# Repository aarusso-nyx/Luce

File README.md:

# Luce Firmware

ESP32 firmware project built with PlatformIO + ESP-IDF.

> `scripts/luce.sh` refreshes PlatformIO discovery, including sourcing your `~/.zshrc` environment when required.

## Build/Flash/Monitor

Use the repository scripts for deterministic local workflows:

```bash
source ~/.zshrc
./scripts/luce.sh build                    # build all environments
./scripts/luce.sh upload --env default      # flash a specific environment
./scripts/luce.sh monitor --env default     # serial monitor with timestamps
./scripts/luce.sh test --layers all --env net1 --host https://<device-ip> --http-token <token> --tcp-token <cli-token>
```
You can also call PlatformIO directly when preferred. Use `pio` when available; use `python3 -m platformio` only when the module is installed in the active Python.

For Python contract-test dependencies, use a local virtual environment:

```bash
python3 -m venv .venv
.venv/bin/python -m pip install -r tests/requirements.txt
```

## Serial Ports and Runtime Iteration

Operational serial port policy for Luce CORE/NET workflows:

- Flash/upload port: `/dev/cu.usbserial-0001`
- Mirror monitor/console port: `/dev/cu.usbserial-40110`

Use the following exact commands unless the port assignment is changed intentionally:

```bash
pio run -e default -t upload --upload-port /dev/cu.usbserial-0001
pio device monitor -p /dev/cu.usbserial-40110
pio run -e net0 -t upload --upload-port /dev/cu.usbserial-0001
```

Autonomous firmware iteration:

```bash
source ~/.zshrc
./scripts/luce.sh build --env <env>
./scripts/luce.sh upload --env <env> --upload-port /dev/cu.usbserial-0001
./scripts/luce.sh monitor --env <env> --monitor-port /dev/cu.usbserial-40110
```

For `net0`, run CLI commands (`help`, `status`, `nvs_dump`, `i2c_scan`, `mcp_read`, `relay_set`, `relay_mask`, `buttons`, `lcd_print`, `reboot`) and collect the first 80 monitor lines after reset.

Monitor fallback (if termios fails on this host):

```bash
python3 - <<'PY'
import sys, serial
with serial.Serial('/dev/cu.usbserial-40110', 115200, timeout=0.2) as ser:
    for _ in range(80):
        line = ser.readline()
        if line:
            sys.stdout.write(line.decode('utf-8', errors='replace'))
PY
```

## Feature flags

`LUCE_NET_*` selects network feature groups in `build_flags`.

- `default` — no `LUCE_NET_*` flags (baseline): NVS, I2C, LCD, CLI
- `net0` — `-DLUCE_NET_CORE=1`: baseline + Wi-Fi + NTP + mDNS + TCP CLI
- `net1` — `-DLUCE_NET_CORE=1 -DLUCE_NET_MQTT=1 -DLUCE_NET_HTTP=1 -DLUCE_NET_OTA=1`: net0 + MQTT + HTTP + OTA

In `scripts/luce.sh build`, `LUCE_ENV` can optionally build a single env. If unset, all declared envs are built.
Default PlatformIO environment is `default`.
Canonical SDK config is a single file: `sdkconfig` (shared across all envs).

Ports used by bootstrap scripts:
```bash
Upload:  /dev/cu.usbserial-0001
Monitor: /dev/cu.usbserial-40110
```

## Documentation Locations

- Product/architecture/operations docs: `docs/user/`
- Governance evidence: `docs/governance/audit/`, `docs/governance/health/`, `docs/governance/compliance/`
- Scratch investigation/diagnostics/plans: `docs/work/inv/`, `docs/work/diag/`, `docs/work/plan/`

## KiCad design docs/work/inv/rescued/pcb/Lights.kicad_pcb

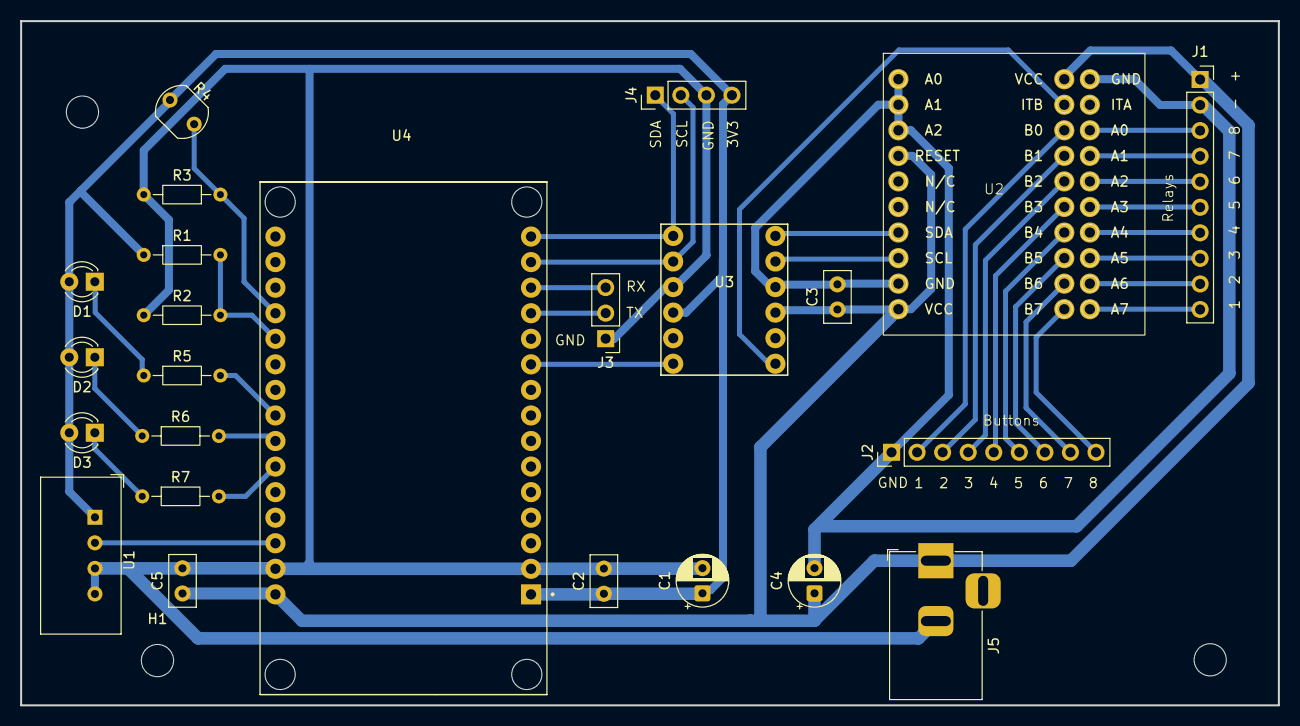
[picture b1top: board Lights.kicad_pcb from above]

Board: 2 copper layers, 125.0 x 68.0 mm, 27 parts (0 on the bottom side), 36 nets.

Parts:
C1, C4: 100µF; CP_Radial_D5.0mm_P2.50mm
C2, C3, C5: 100nF; C_Disc_D5.0mm_W2.5mm_P2.50mm
D1, D2, D3: LED; LED_D3.0mm
H1, H2, H3: MountingHole; MountingHole_3.2mm_M3
J1: Relays; PinSocket_1x10_P2.54mm_Vertical
J2: BUTTONS; PinHeader_1x09_P2.54mm_Vertical
J3: UART; PinHeader_1x03_P2.54mm_Vertical
J4: I2C; PinHeader_1x04_P2.54mm_Vertical
J5: Jack-DC; BarrelJack_Horizontal
R1, R2: 100k; R_Axial_DIN0204_L3.6mm_D1.6mm_P7.62mm_Horizontal
R3: 47k; R_Axial_DIN0204_L3.6mm_D1.6mm_P7.62mm_Horizontal
R4: LDR07; R_LDR_5.1x4.3mm_P3.4mm_Vertical
R5, R6, R7: 470; R_Axial_DIN0204_L3.6mm_D1.6mm_P7.62mm_Horizontal
U1: AM2302; ASAIR_AM2302_P2.54mm_Vertical
U2: CJMCU-2317; MCP23017
U3: BSS138_4ch; BSS138
U4: ESP32-DEVKIT-V1; MODULE_ESP32_DEVKIT_V1

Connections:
+3V3: C1.1, C2.1, D1.2 (A), D2.2 (A), D3.2 (A), J4.4 (3.3V), R1.1, R4.1, U1.1 (VDD), U3.10 (LV), U4.1 (3V3)
+5V: C3.1, C4.1, C5.1, J1.1 (+5V), J5.1, U2.4 (RESET), U2.10 (VCC), U2.11 (VCC), U3.3 (HV), U4.30 (VIN)
GND: C1.2, C2.2, C3.2, C4.2, C5.2, J1.2 (GND), J2.1 (GND), J3.1 (GND), J4.3 (GND), J5.2, R2.2, R3.2, U1.3 (GND), U1.4 (GND), U2.1 (A0), U2.2 (A1), U2.3 (A2), U2.9 (GND), U2.12 (GND), U3.4 (GND), U3.9 (GND), U4.2 (GND), U4.29 (GND)
unnamed: D1.1 (K), R5.1
unnamed: D2.1 (K), R6.1
unnamed: D3.1 (K), R7.1
unnamed: J1.3 (CH1), U2.16 (A0)
unnamed: J1.4 (CH2), U2.18 (A1)
unnamed: J1.5 (CH3), U2.20 (A2)
unnamed: J1.6 (CH4), U2.22 (A3)
unnamed: J1.7 (CH5), U2.24 (A4)
unnamed: J1.8 (CH6), U2.26 (A5)
unnamed: J1.9 (CH7), U2.28 (A6)
unnamed: J1.10 (CH8), U2.30 (A7)
unnamed: J2.2 (B1), U2.15 (B0)
unnamed: J2.3 (B2), U2.17 (B1)
unnamed: J2.4 (B3), U2.19 (B2)
unnamed: J2.5 (B4), U2.21 (B3)
unnamed: J2.6 (B5), U2.23 (B4)
unnamed: J2.7 (B6), U2.25 (B5)
unnamed: J2.8 (B7), U2.27 (B6)
unnamed: J2.9 (B8), U2.29 (B7)
unnamed: J3.3 (RX), U4.13 (TX0)
unnamed: J3.2 (TX), U4.12 (RX0)
unnamed: J4.2 (SCL), U3.8 (LV3), U4.14 (D22)
unnamed: J4.1 (SDA), U3.7 (LV4), U4.15 (D23)
unnamed: U1.2 (SDA), U4.28 (D13)
unnamed: U2.13 (ITB), U3.1 (HV1)
unnamed: U2.8 (SCL), U3.5 (HV3)
unnamed: U2.7 (SDA), U3.6 (HV4)
unnamed: U3.12 (LV1), U4.10 (D19)
unnamed: R5.2, U4.23 (D25)
unnamed: R6.2, U4.24 (D26)
unnamed: R7.2, U4.25 (D27)
unnamed: R3.1, R4.2, U4.19 (D34)
unnamed: R1.2, R2.1, U4.20 (D35)

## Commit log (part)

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2026-02-22 "chore(inv): add rescued PCB + docs (reference only)"
2026-02-22 chore: bootstrap governance and build scripts
2026-02-22 chore(inv): add hardware map and open questions
2026-02-22 feat(stage0): minimal boot + reset reason + heap diagnostics
2026-02-22 docs: persist serial port defaults
2026-02-22 docs: persist serial monitor fallback
2026-02-22 chore: default serial ports in flash and monitor scripts
2026-02-22 docs: enforce monitor port default in agent workflow
2026-02-22 feat(stage1): NVS init + device/app info + NVS dump
2026-02-22 feat(stage2): I2C scan + MCP23017 relays/buttons diagnostics
2026-02-22 feat(stage3): LCD status output (optional) + mirrored console logs
2026-02-22 feat(stage4): serial CLI (no networking) for diagnostics/control
2026-02-22 chore(hil): add reproducible bench playbook + log capture script
2026-02-22 docs(governance): add npm non-applicability rationale
2026-02-22 chore: finalize governance and workspace evidence artifacts
2026-02-22 chore: persist local governance evidence artifacts
2026-02-22 chore(tooling): stabilize lint/static checks
2026-02-22 test: add minimal host unit test harness
2026-02-22 chore(diag): add robust serial capture for evidence chain
2026-02-22 fix(stage4): stabilize runtime + CLI e2e baseline
2026-02-22 refactor: centralize startup status and I2C flow
2026-02-22 chore(gate): Phase 2 entry criteria satisfied (evidence attached)
2026-02-22 docs+tests: persist open hardware assumptions and remove shim
2026-02-22 feat(stage5): wifi lifecycle bring-up (no services)
2026-02-22 test(stage5): add HIL Wi-Fi lifecycle evidence capture plan
2026-02-22 chore(plan): prune outdated stage5 planning docs
2026-02-22 chore(plan): prune stale Phase-2 plan checklists
2026-02-22 chore(stage5): evidence chain PASS
2026-02-22 docs: promote hardware-map to canonical docs/dev location
2026-02-22 fix(lint,tests): stabilize stage5 CLI
2026-02-22 feat(stage6): add SNTP time sync (non-blocking)
2026-02-22 feat(stage7): add mDNS advertiser (optional)
2026-02-22 chore(stage7): capture evidence chain
2026-02-22 feat(stage9): mqtt telemetry client (publish-only, tls optional)
2026-02-23 feat(stage10): https server read-only (secure only)
2026-02-23 chore(stage10): capture evidence chain
2026-02-23 docs(plan): modularization plan for splitting main.cpp
2026-02-23 refactor(main.cpp): S0 inventory map (no behavior change)
2026-02-23 chore(evidence): capture modularization verification (S0)
2026-02-23 chore(governance): post-implementation realignment (evidence local)
2026-02-23 docs: canonicalize product docs under docs/user
2026-02-23 docs(plan): update main.cpp modularization plan (current monolith)
2026-02-23 chore: close governance gap closure path for NCI 100
2026-02-23 chore: ignore .agent tmp outputs
2026-02-23 docs: consolidate LUCE canonical doc and governance references
2026-02-23 chore(governance): archive historical scorecards
2026-02-23 refactor: split app entrypoint and diagnostics modules
2026-02-23 refactor: complete runtime split and stabilize CLI parsing
2026-02-23 feat(stage5): add wifi lifecycle and stage6 ntp modules
2026-02-23 docs(plan): expand stage plan for wifi, ntp and next stages
2026-02-23 fix: stabilize stage8-10 networking modules and CLI entrypoints
2026-02-23 feat(stage7): add mDNS TXT records and failed-state logging
2026-02-23 fix(stage8): prevent cli_net task return
2026-02-23 fix(stage8): guard TCP listener setup until IP stack ready
2026-03-01 Stage consolidation
2026-03-01 Simplify
2026-03-01 New Governance
2026-03-01 Clean up
2026-03-01 Clean up 2
2026-03-01 dried
2026-03-01 scripting
2026-03-01 Realign
2026-03-01 closing gaps
2026-03-01 Cleaned
2026-03-01 tests suites
2026-03-01 Adherence
2026-03-01 Doc tests
2026-03-01 Adherent
2026-03-01 Ready to Test
2026-05-28 Harden HTTPS certificate workflow
2026-05-28 Adopt device CSR HTTPS provisioning
2026-05-29 Add Wave A foundation scaffolding
2026-05-29 Implement Wave B core correctness
2026-05-29 Implement Wave C adoption sweep
2026-05-29 Implement Wave D PKI infrastructure
2026-05-29 Implement Wave E quality gates
2026-05-29 Refresh Wave E evidence manifest
2026-05-29 Implement Wave F residual hardening
2026-05-29 Refresh Wave F evidence manifest
